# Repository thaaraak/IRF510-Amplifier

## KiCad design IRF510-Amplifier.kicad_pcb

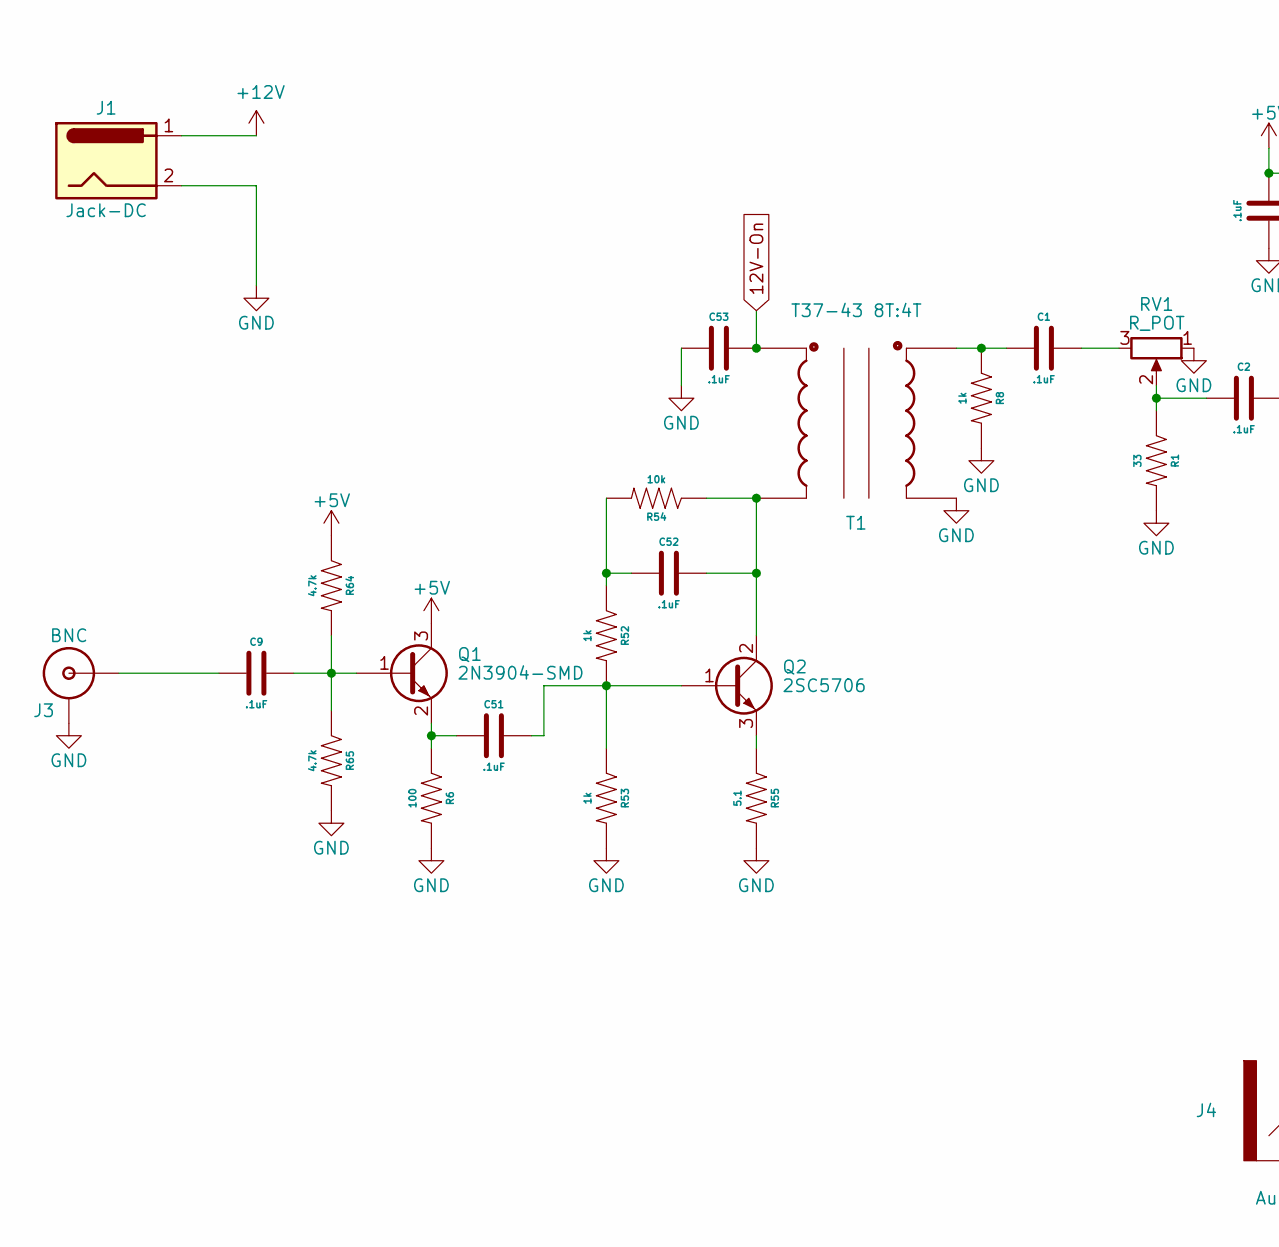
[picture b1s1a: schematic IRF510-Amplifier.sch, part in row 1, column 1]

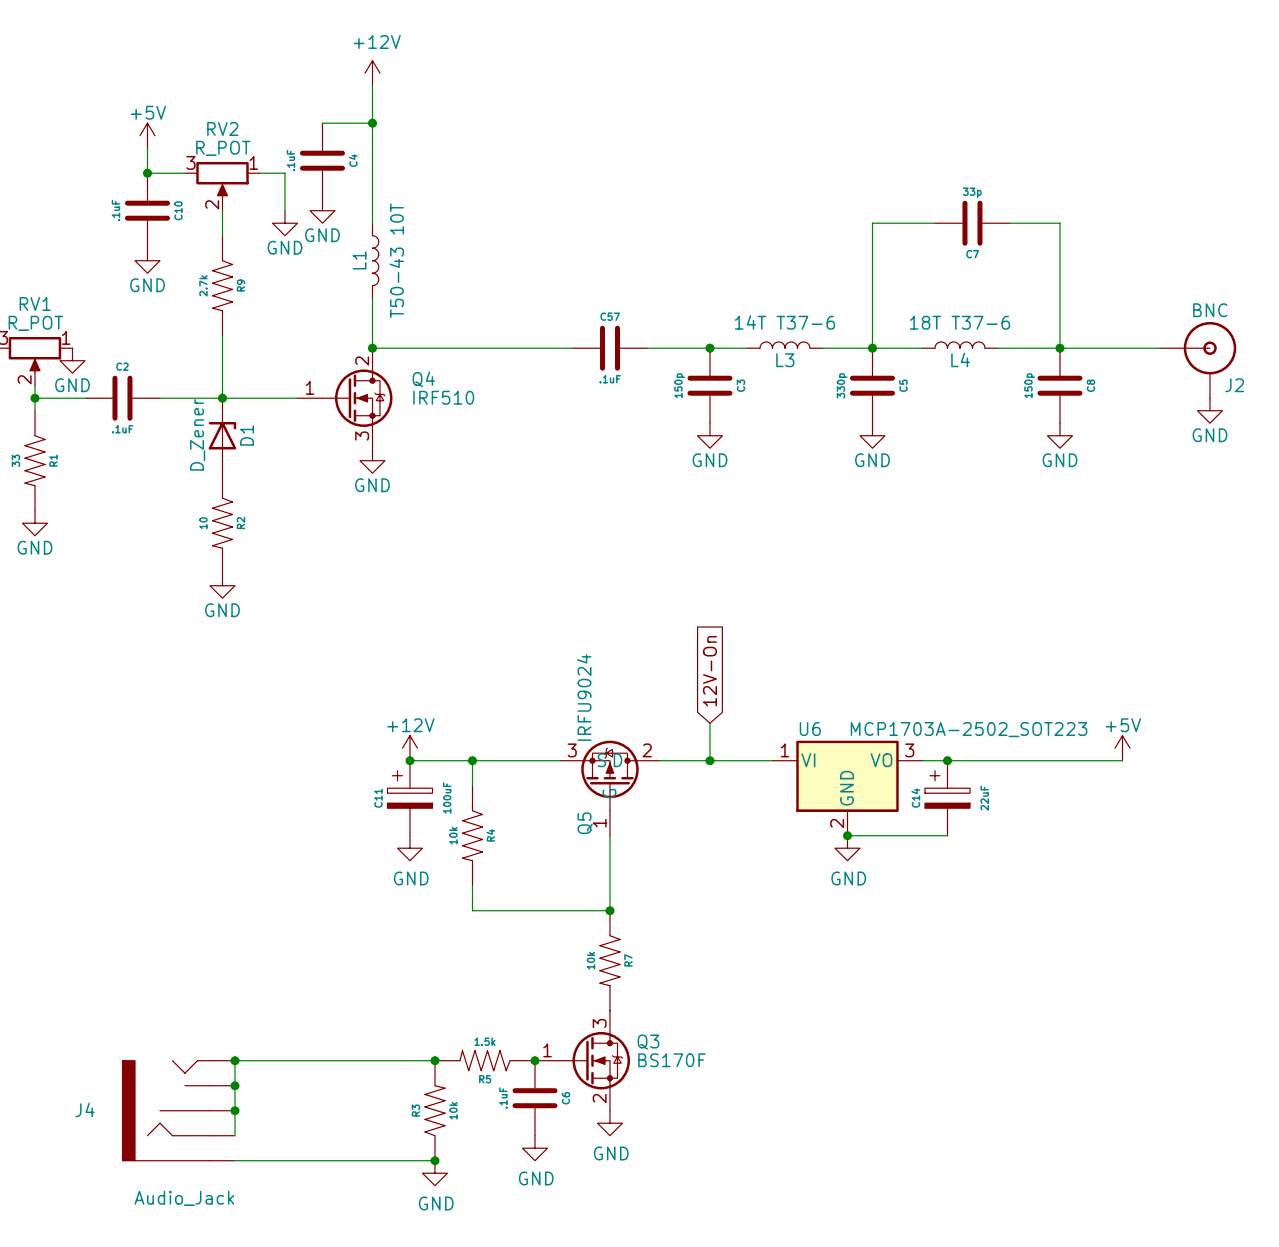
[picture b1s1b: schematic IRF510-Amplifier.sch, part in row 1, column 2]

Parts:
C1, C2, C4, C6, C9, C10, C51, C52, C53, C57: .1uF; Capacitor 0805
C3, C8: 150p; Capacitor 1206
C5: 330p; Capacitor 1206
C7: 33p; Capacitor 1206
C11: 100uF; Cap_6.3x5.4
C14: 22uF; Cap_4x5.4
D1: D_Zener; D_A-405_P10.16mm_Horizontal
J1: Jack-DC; BarrelJack_Horizontal
J2, J3: BNC
J4: Audio_Jack
L1: T50-43 10T; T50_Inductor
L3: 14T T37-6; T37_Inductor
L4: 18T T37-6; T37_Inductor
Q1: 2N3904-SMD; SOT-23
Q2: 2SC5706; TO-252-2
Q3: BS170F; SOT-23
Q4: IRF510; TO-220-3_Vertical
Q5: IRFU9024; TO-251-3_Vertical
R1: 33; Resistor 0805
R2: 10; Resistor 0805
R3, R4, R7, R54: 10k; Resistor 0805
R5: 1.5k; Resistor 0805
R6: 100; Resistor 0805
R8, R52, R53: 1k; Resistor 0805
R9: 2.7k; Resistor 0805
R55: 5.1; Resistor 0805
R64, R65: 4.7k; Resistor 0805
RV1, RV2: R_POT; Trimpot Vertical
T1: T37-43 8T:4T; T37 Transformer
U6: MCP1703A-2502_SOT223; TO-252-3_TabPin2

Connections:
12V-On: C53.1, Q5.2 (D), T1.C1B, U6.1 (VI)
+5V: C10.1, C14.1, Q1.3 (C), R64.1, RV2.3, U6.3 (VO)
+12V: C4.1, C11.1, J1.1, L1.1, Q5.3 (S), R4.1
GND: C3.2, C4.2, C5.2, C6.2, C8.2, C10.2, C11.2, C14.2, C53.2, J1.2, J2.GND, J3.GND, J4.SLEEVE, Q3.2 (S), Q4.3 (S), R1.2, R2.2, R3.1, R6.2, R8.2, R53.2, R55.2, R65.2, RV1.1, RV2.1, T1.C2A, U6.2 (GND)
unnamed: C1.1, R8.1, T1.C2B
unnamed: C1.2, RV1.3
unnamed: C2.1, R1.1, RV1.2
unnamed: C2.2, D1.1 (K), Q4.1 (G), R9.2
unnamed: C3.1, C57.2, L3.1
unnamed: C5.1, C7.2, L3.2, L4.1
unnamed: C6.1, Q3.1 (G), R5.1
unnamed: C7.1, C8.1, J2.S (OUT), L4.2
unnamed: C9.1, J3.S (OUT)
unnamed: C9.2, Q1.1 (B), R64.2, R65.1
unnamed: C51.1, Q1.2 (E), R6.1
unnamed: C51.2, Q2.1 (B), R52.2, R53.1
unnamed: C52.1, R52.1, R54.2
unnamed: C52.2, Q2.2 (C), R54.1, T1.C1A
unnamed: C57.1, L1.2, Q4.2 (D)
unnamed: D1.2 (A), R2.1
unnamed: J4.RING, J4.RSH, J4.TIP, J4.TSH, R3.2, R5.2
unnamed: Q2.3 (E), R55.1
unnamed: Q3.3 (D), R7.2
unnamed: Q5.1 (G), R4.2, R7.1
unnamed: R9.1, RV2.2

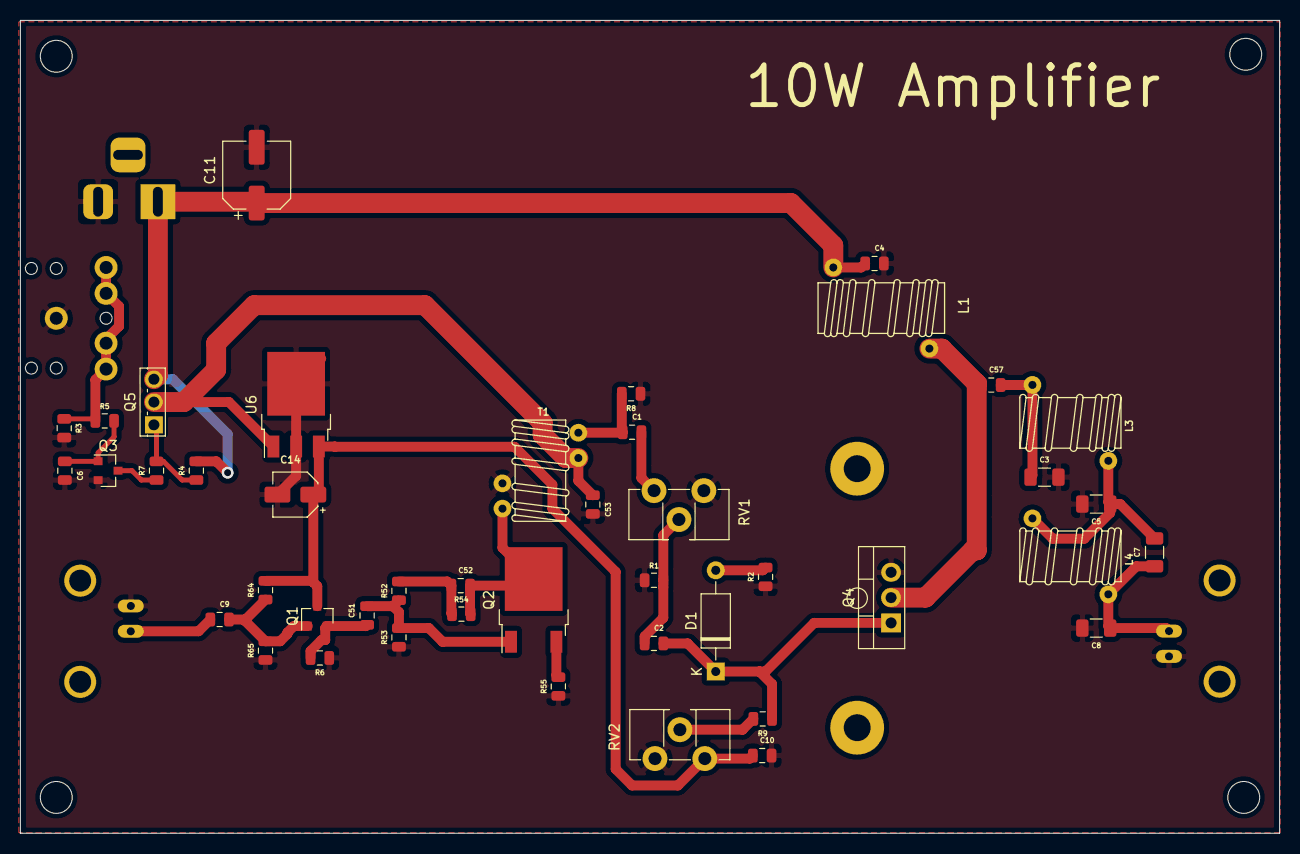
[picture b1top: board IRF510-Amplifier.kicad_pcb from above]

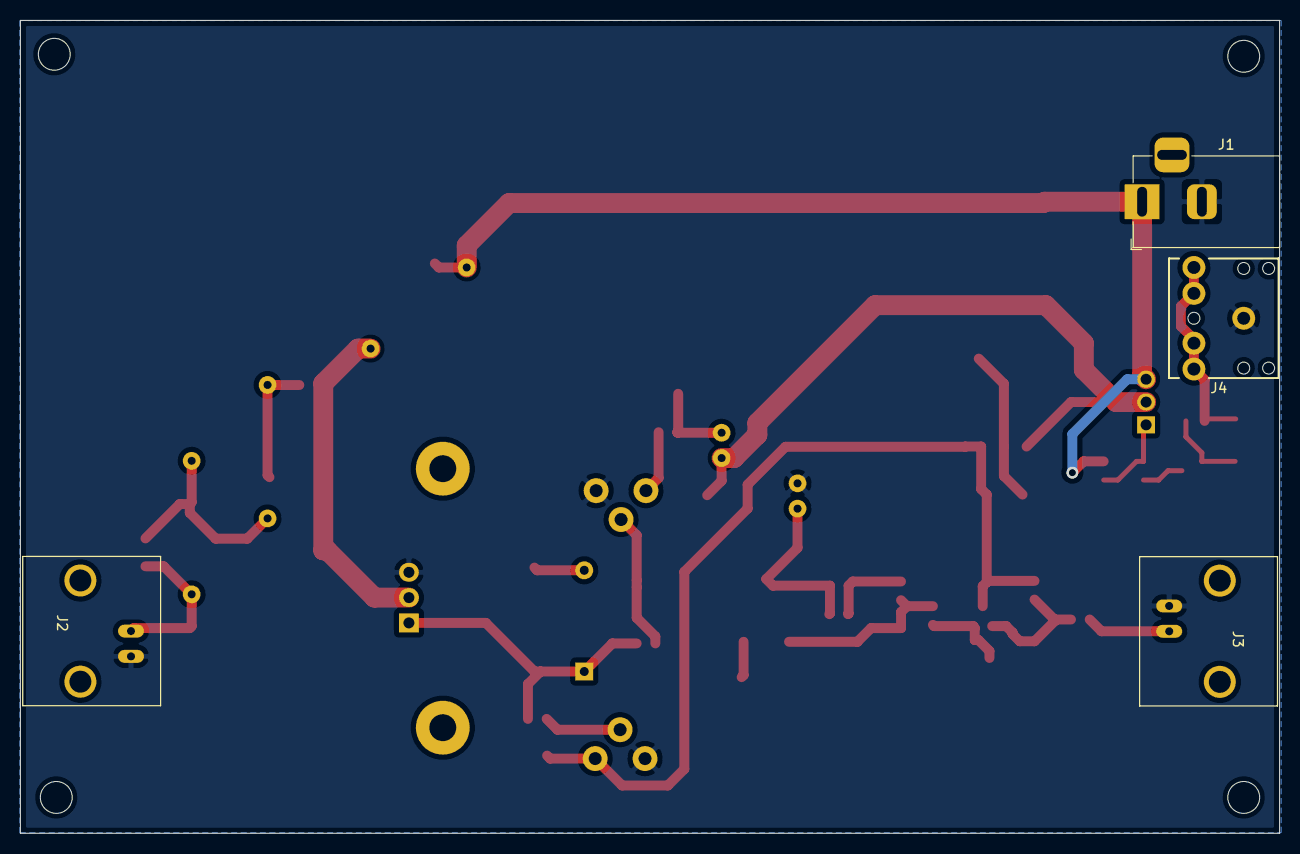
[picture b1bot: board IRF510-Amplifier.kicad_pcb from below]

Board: 2 copper layers, 126.4 x 81.6 mm, 53 parts (4 on the bottom side), 25 nets.

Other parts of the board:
 : MountingHole_3.2mm_M3
 #2,  #3,  #4: MountingHole_3.2mm_M3
 #5: Heatsink_Mounting_25mm

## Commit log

2021-07-16 reorg
2021-07-16 added gerber
2021-07-18 updates after 1st test
